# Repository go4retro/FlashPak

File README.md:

# FlashPak - 512kB FLASH ROM Cartridge Unit for the TANDY Color Computer 1, 2, 3, and Dragon

This cartridge supports 512kB of system programmable FLASH ROM utilizing the RoboCop (Zumwalt) banking system.

## Technical Details
Banks are 16kB in size (technically, 16KiB - 256 bytes, since $ff00-$ffff is reserved for IO and vectors), which allows operation on all TANDY Color Computer models and the Dragon Data Dragon machines.  FLASH ROM appears at location $c000 in the memory map, while the banking register appears at $ff40.  The bits in the banking register are as follows:

| IO Location | Bit Location | Description                 |
| ----------- | ------------ | --------------------------- |
| $ff40       | 4:0          | FLASH address lines A18-A14 |
|             | 7            | 1 = Programming Enabled     |

The system is designed to utilize AM29F040B FLASH ROMs, but can also accommodate 16kB-512kB FLASH ROMs or EPROMs via J1-J5.  Please see schematic for more details.  If EPROMs are utilized, IC3 is not required (EPROMs cannot be system programmable)

To program please consult the AM29F040B datasheet for details, but essentially:

* set bit 7 to 1 and select bank in bank register
* via machine language, store the following values:
* store $aa in $c555
* store $55 in $c2aa
* store $a0 in $c555
* store desired value in $c000-$feff address ($fdff on Color Computer 3, I believe)

Sample stub code is available in the src/ directory.  The programming must be precise and cannot easily be performed from BASIC[1].

[1]: To simplify construction and reduce cost, programming is enabled for all of $c000-$ffff.  This includes the entire $ffxx IO region.  Unless care is taken to disable BASIC or the IRQ handlers from accessing $ffxx regions while sending the special programming sequence, the sequence will be disrupted and programming will not occur.

## Photos

## License
Copyright (C) 2021  RETRO Innovations

These files are free designs; you can redistribute them and/or modify
them under the terms of the Creative Commons Attribution-ShareAlike 
4.0 International License.

You should have received a copy of the license along with this
work. If not, see <http://creativecommons.org/licenses/by-sa/4.0/>.

These files are distributed in the hope that they will be useful,
but WITHOUT ANY WARRANTY; without even the implied warranty of
MERCHANTABILITY or FITNESS FOR A PARTICULAR PURPOSE.  See the
license for more details.

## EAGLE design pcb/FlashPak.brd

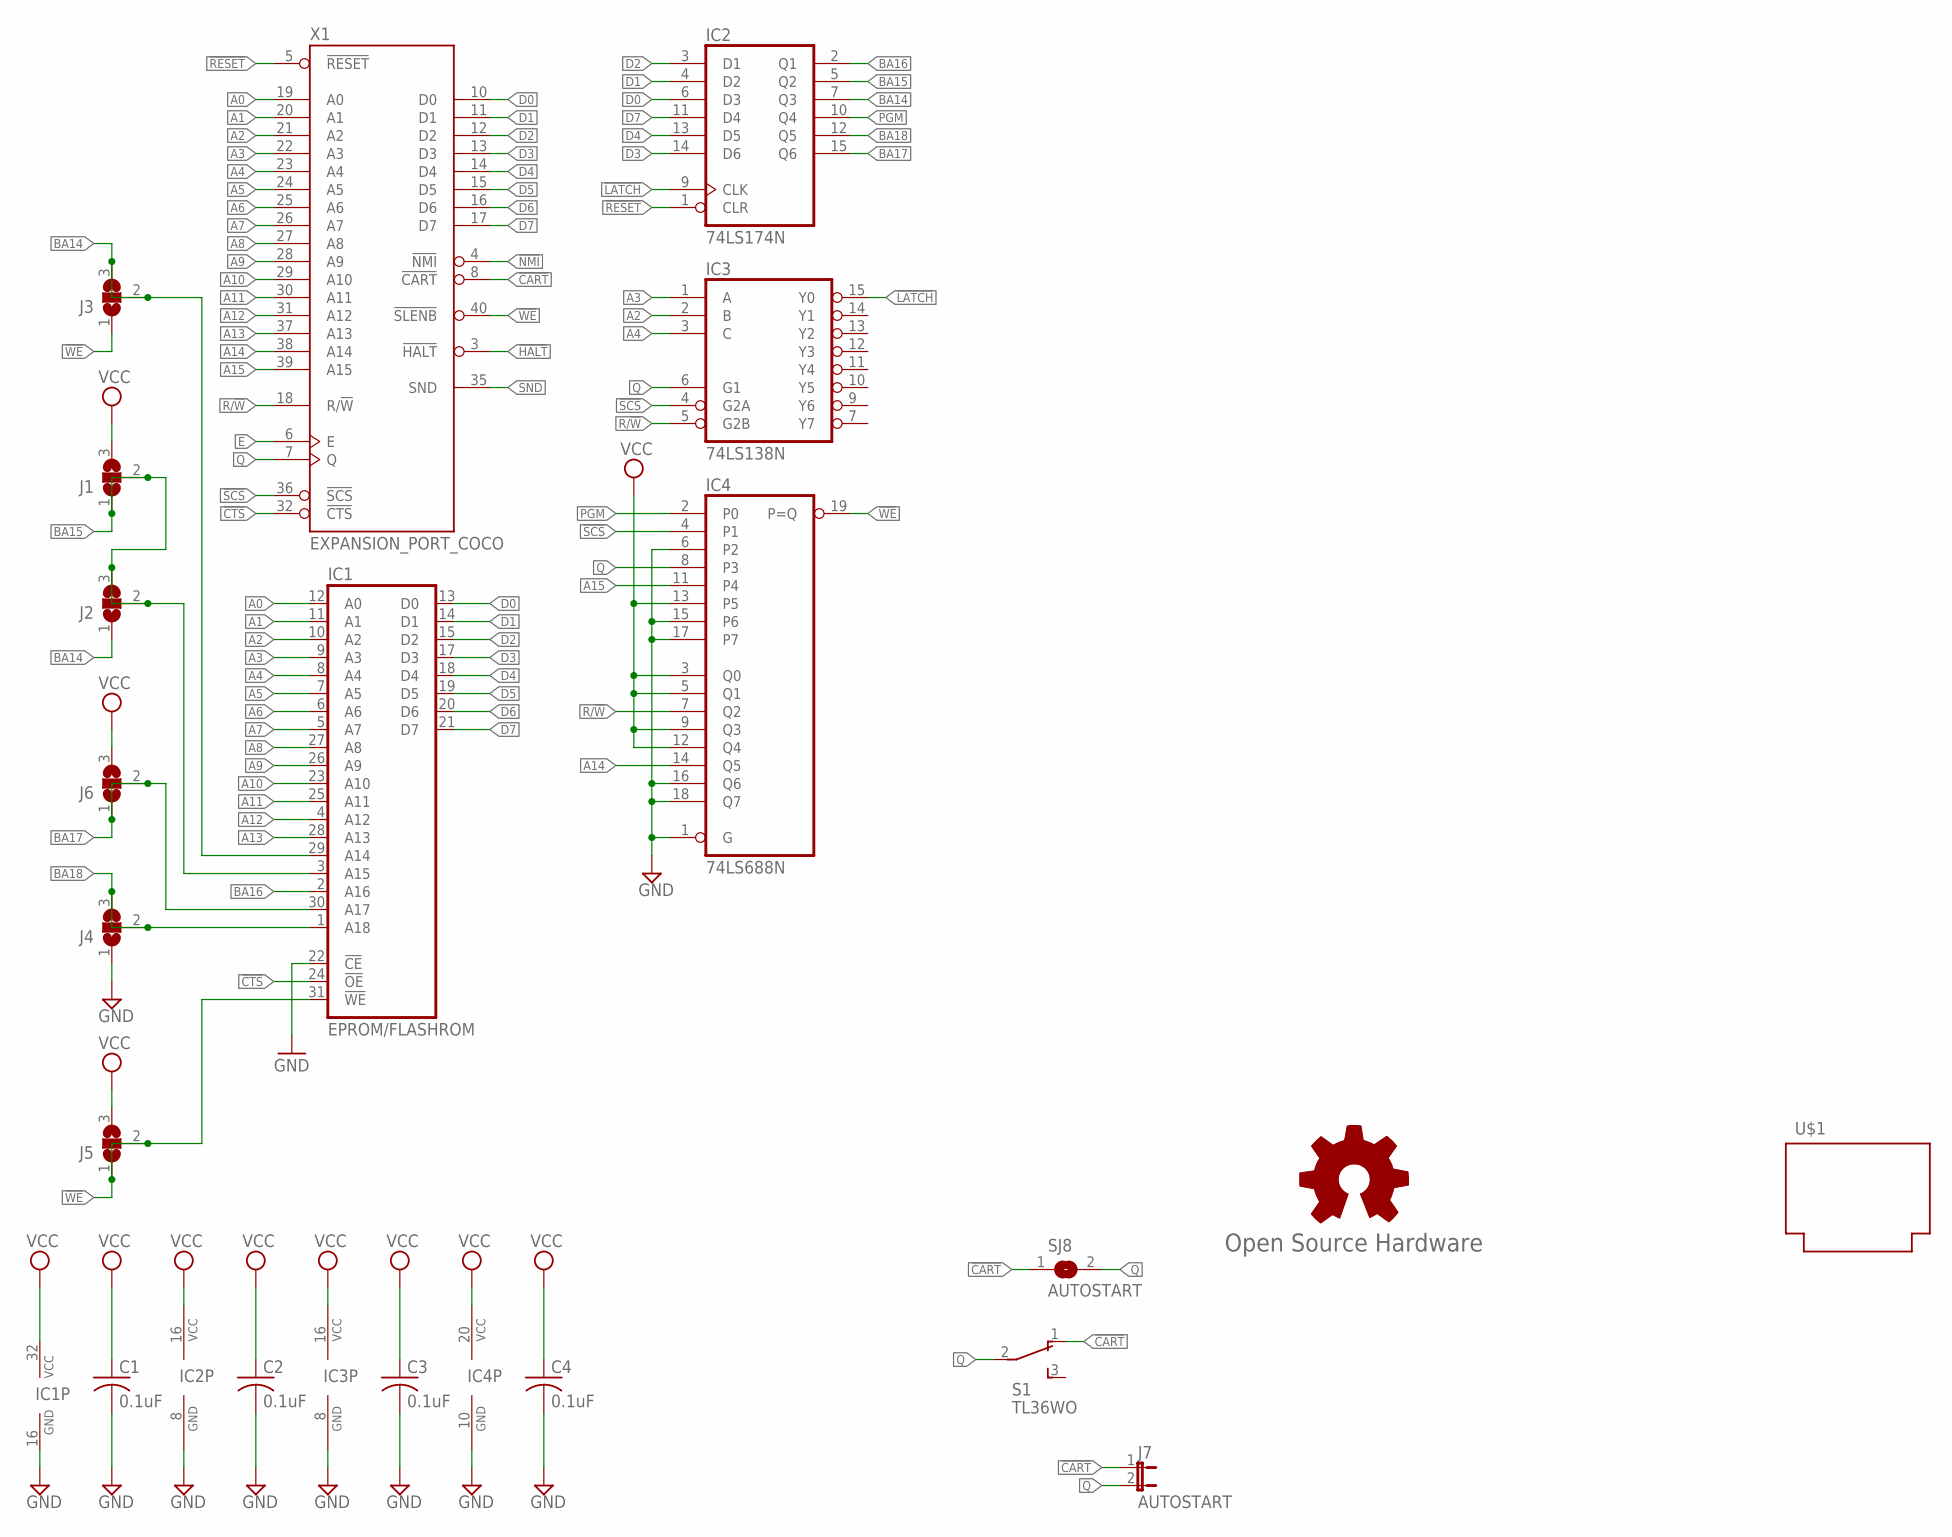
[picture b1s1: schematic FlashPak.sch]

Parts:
C1, C2, C3, C4: 0.1uF; C025-025X050
GOLD_ORB_SM1: Open Source Hardware; OSHW_8MM
IC1: EPROM/FLASHROM; DIL32-RP
IC2: 74LS174N; DIL16-RP
IC3: 74LS138N; DIL16-RP
IC4: 74LS688N; DIL20-RP
J1, J2, J3, J4, J5, J6: SJ2W; SJ_2
J7: AUTOSTART; JP1
S1: TL36WO; TL3XWO
SJ8: AUTOSTART; SJ
U$1: PROGRAM_PAK
X1: EXPANSION_PORT_COCO; MA20-2

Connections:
!CART: J7.1, S1.1 (O), SJ8.1, X1.8 (!CART)
!CTS: IC1.24 (!OE), X1.32 (!CTS)
!HALT: X1.3 (!HALT)
!LATCH: IC2.9 (CLK), IC3.15 (Y0)
!NMI: X1.4 (!NMI)
!RESET: IC2.1 (CLR), X1.5 (!RESET)
!SCS: IC3.4 (G2A), IC4.4 (P1), X1.36 (!SCS)
!WE: IC1.31 (!WE), IC4.19 (P=Q), J3.1, J5.1, J5.2, X1.40 (!SLENB)
+12V: X1.2 (+12V)
-12V: X1.1 (-12V)
A0: IC1.12 (A0), X1.19 (A0)
A1: IC1.11 (A1), X1.20 (A1)
A2: IC1.10 (A2), IC3.2 (B), X1.21 (A2)
A3: IC1.9 (A3), IC3.1 (A), X1.22 (A3)
A4: IC1.8 (A4), IC3.3 (C), X1.23 (A4)
A5: IC1.7 (A5), X1.24 (A5)
A6: IC1.6 (A6), X1.25 (A6)
A7: IC1.5 (A7), X1.26 (A7)
A8: IC1.27 (A8), X1.27 (A8)
A9: IC1.26 (A9), X1.28 (A9)
A10: IC1.23 (A10), X1.29 (A10)
A11: IC1.25 (A11), X1.30 (A11)
A12: IC1.4 (A12), X1.31 (A12)
A13: IC1.28 (A13), X1.37 (A13)
A14: IC4.14 (Q5), X1.38 (A14)
A15: IC4.11 (P4), X1.39 (A15)
BA14: IC1.29 (A14), IC2.7 (Q3), J2.1, J3.2, J3.3
BA15: IC1.3 (A15), IC2.5 (Q2), J1.1, J1.2, J2.2, J2.3
BA16: IC1.2 (A16), IC2.2 (Q1)
BA17: IC1.30 (A17), IC2.15 (Q6), J6.1, J6.2
BA18: IC1.1 (A18), IC2.12 (Q5), J4.2, J4.3
D0: IC1.13 (D0), IC2.6 (D3), X1.10 (D0)
D1: IC1.14 (D1), IC2.4 (D2), X1.11 (D1)
D2: IC1.15 (D2), IC2.3 (D1), X1.12 (D2)
D3: IC1.17 (D3), IC2.14 (D6), X1.13 (D3)
D4: IC1.18 (D4), IC2.13 (D5), X1.14 (D4)
D5: IC1.19 (D5), X1.15 (D5)
D6: IC1.20 (D6), X1.16 (D6)
D7: IC1.21 (D7), IC2.11 (D4), X1.17 (D7)
E: X1.6 (E)
GND: C1.2, C2.2, C3.2, C4.2, IC1.16 (GND), IC1.22 (!CE), IC2.8 (GND), IC3.8 (GND), IC4.1 (G), IC4.6 (P2), IC4.10 (GND), IC4.15 (P6), IC4.16 (Q6), IC4.17 (P7), IC4.18 (Q7), J4.1, X1.33 (GND), X1.34 (GND)
PGM: IC2.10 (Q4), IC4.2 (P0)
Q: IC3.6 (G1), IC4.8 (P3), J7.2, S1.2, SJ8.2, X1.7 (Q)
R/!W: IC3.5 (G2B), IC4.7 (Q2), X1.18 (R/!W)
SND: X1.35 (SND)
VCC: C1.1, C2.1, C3.1, C4.1, IC1.32 (VCC), IC2.16 (VCC), IC3.16 (VCC), IC4.3 (Q0), IC4.5 (Q1), IC4.9 (Q3), IC4.12 (Q4), IC4.13 (P5), IC4.20 (VCC), J1.3, J5.3, J6.3, X1.9 (VCC)

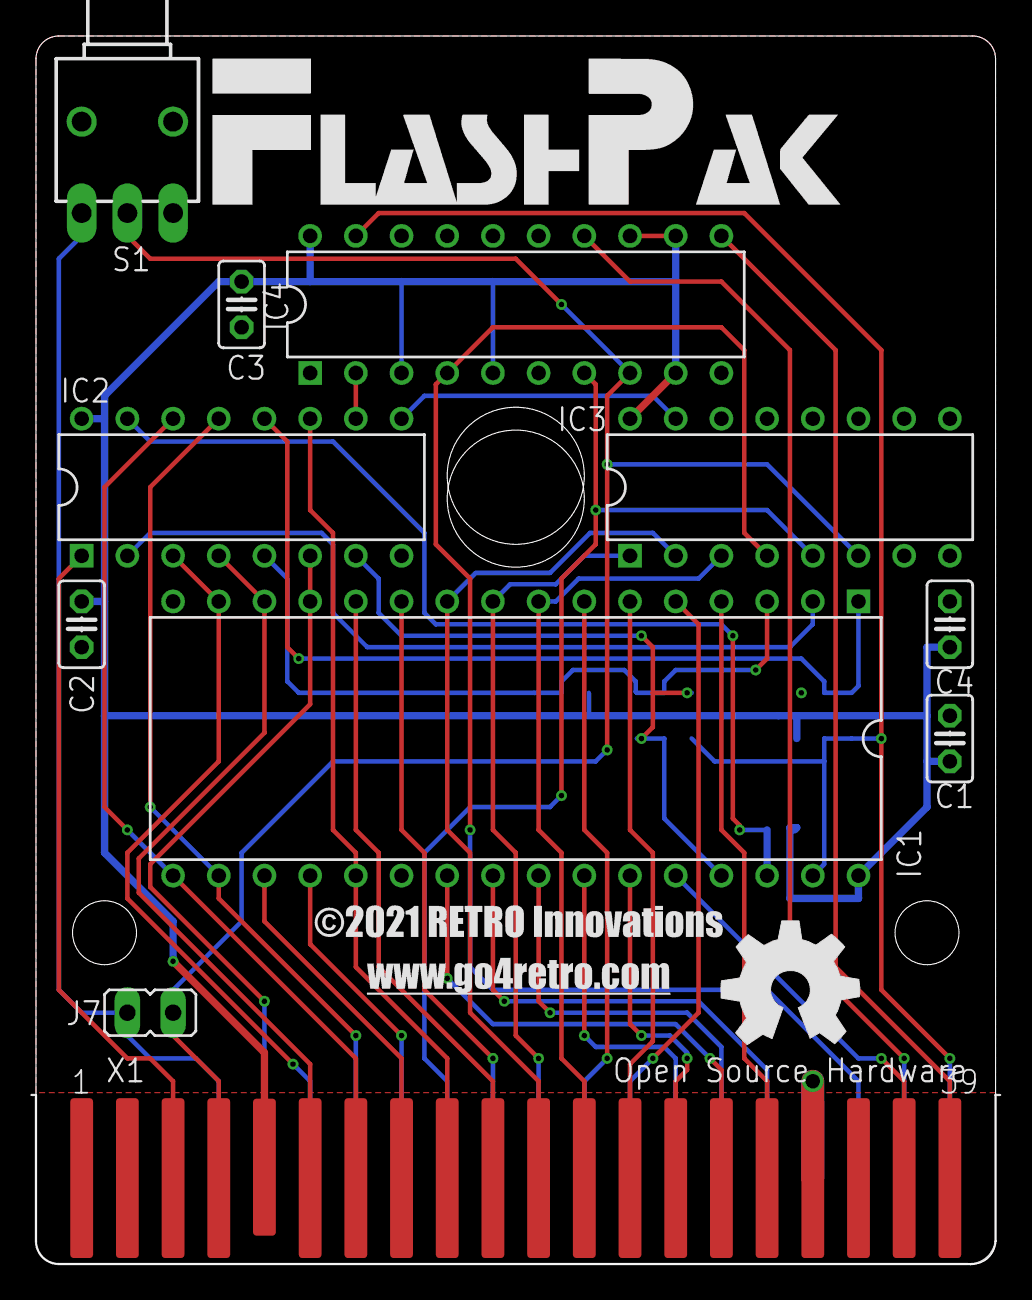
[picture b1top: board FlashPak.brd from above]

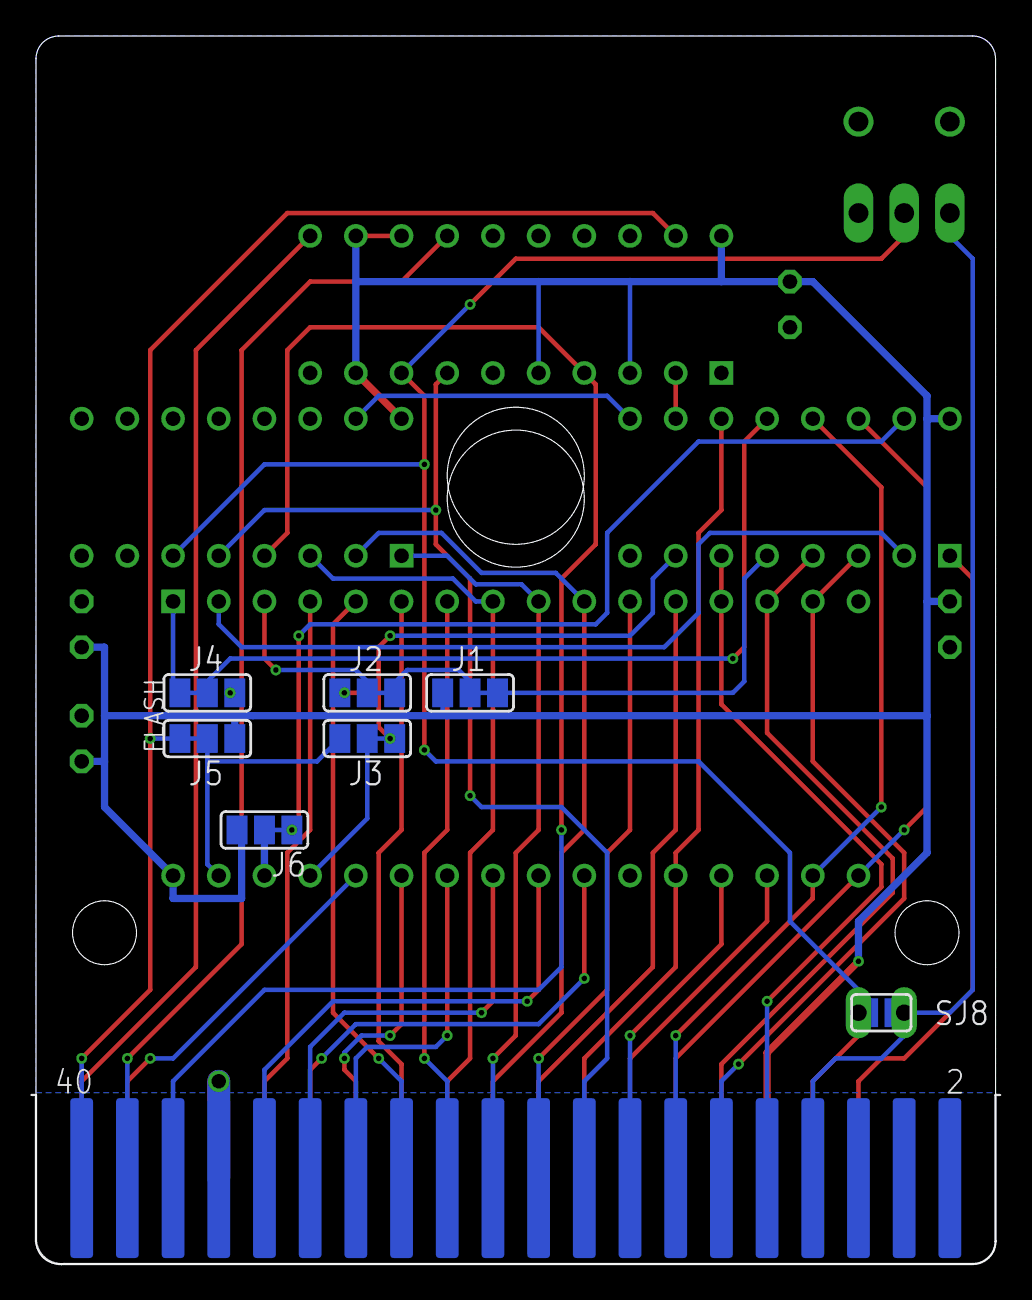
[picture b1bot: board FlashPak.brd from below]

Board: 2 copper layers, 53.3 x 68.3 mm, 20 parts (7 on the bottom side), 40 nets.

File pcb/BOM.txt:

Partlist

Exported from FlashPak.sch at 5/6/2024 11:41 PM

EAGLE Version 7.7.0 Copyright (c) 1988-2016 CadSoft

Assembly variant: 

Part     Value               Device              Package      Library     Sheet

C1       0.1uF               C-US025-025X050     C025-025X050 rcl         1
C2       0.1uF               C-US025-025X050     C025-025X050 rcl         1
C3       0.1uF               C-US025-025X050     C025-025X050 rcl         1
C4       0.1uF               C-US025-025X050     C025-025X050 rcl         1
IC1      EPROM/FLASHROM      SST39SF040APHR      DIL32-RP     memory-sst  1
IC2      74LS174N            74LS174N            DIL16-RP     74xx-us-jlb 1
IC3      74LS138N            74LS138N            DIL16-RP     74xx-us-jlb 1
IC4      74LS688N            74LS688N            DIL20-RP     74xx-us-jlb 1
S1       TL36WO              TL36WO              TL3XWO       switch      1
SJ8      AUTOSTART           SJ                  SJ           jumper-jlb  1

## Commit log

2020-03-05 Fixes to README.md
2020-03-05 More Markdown fixes
2021-01-17 Fixed issue with MPI use, added ASM, and wrote sample BASIC code
2021-01-18 Switch to Makefile
2021-01-19 Read and Store functions now support arbitrary addresses
2021-01-19 Add in initial code to find the cart.
2021-01-22 Initial untested block store and read functions
2021-01-27 Added supported for flashing cart image to ROM!
2021-01-27 Add pic of assembled unit
2021-01-27 More detail on ROM space
2021-01-27 text cleanup
2021-02-01 Added a bit of length to the cartridge design to enable easy AUTOSTART access
2021-03-28 Fix bug where updating bank reg while in write mod causes race condition
2021-05-16 Vcc loop removed, final Gerbers created
2021-06-13 Update filenames and photos
2024-05-07 Add BOM.txt
